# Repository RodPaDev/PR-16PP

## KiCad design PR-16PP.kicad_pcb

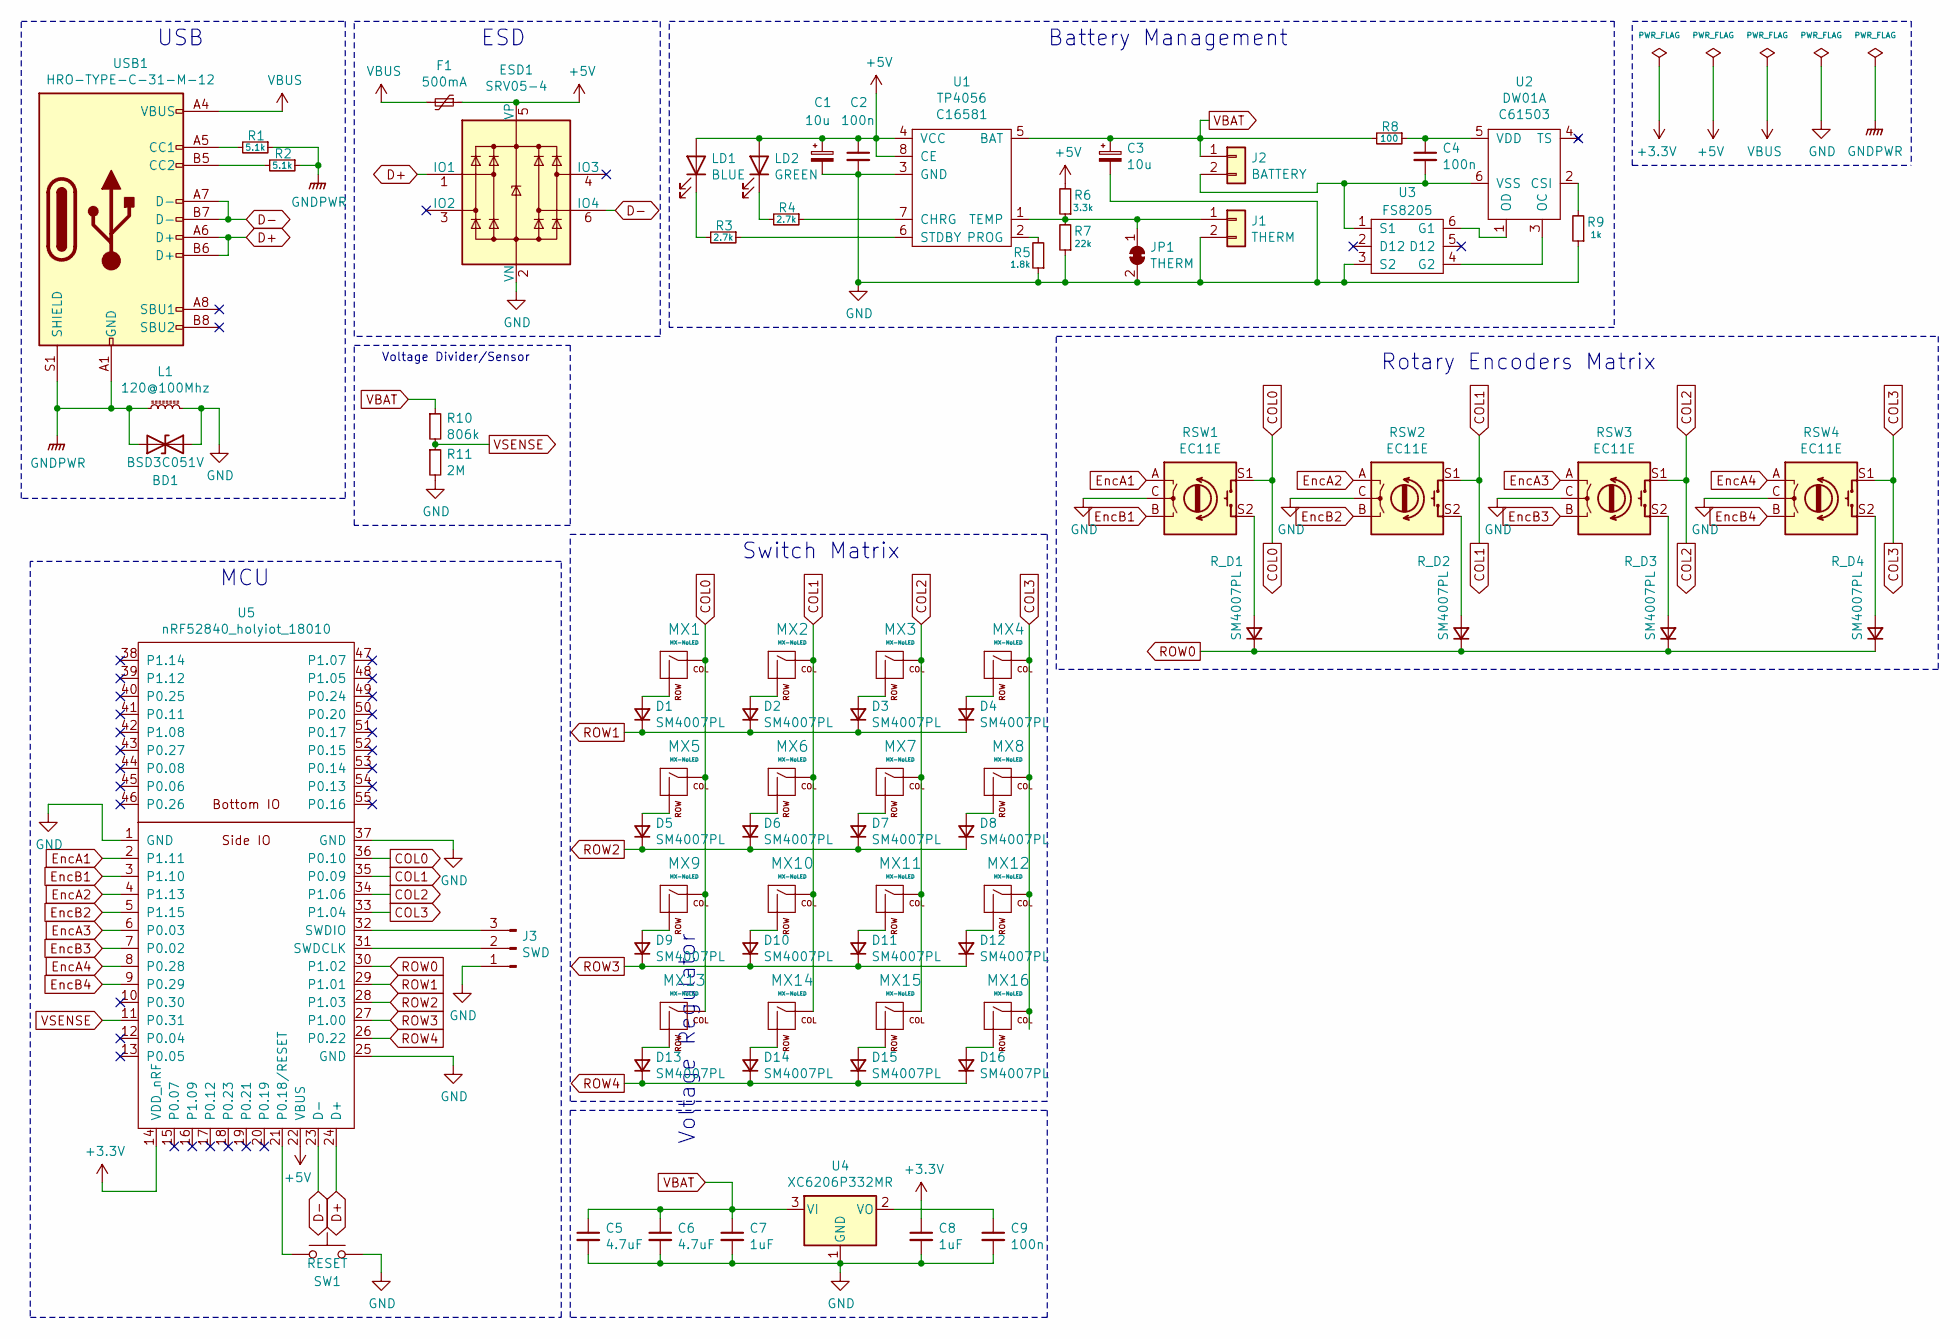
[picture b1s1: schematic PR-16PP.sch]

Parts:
BD1: BSD3C051V; SOT-23_stealth
C1, C3: 10u; C_0603_1608Metric
C2, C4, C9: 100n; C_0603_1608Metric
C5, C6: 4.7uF; C_0603_1608Metric
C7, C8: 1uF; C_0603_1608Metric
D1, D2, D3, D4, D5, D6, D7, D8, D9, D10, D11, D12, D13, D14, D15, D16: SM4007PL; D_SOD-123-Pretty
ESD1: SRV05-4; SOT-23-6
F1: 500mA; Fuse_0603_1608Metric
J1: THERM; JST_SH_SM02B-SRSS-TB_1x02-1MP_P1.00mm_Horizontal
J2: BATTERY; JST_SH_SM02B-SRSS-TB_1x02-1MP_P1.00mm_Horizontal
J3: SWD; PinHeader_1x03_P2.54mm_Vertical
JP1: THERM; SolderJumper-2_P1.3mm_Bridged_RoundedPad1.0x1.5mm
L1: 120@100Mhz; L_0603_1608Metric
LD1: BLUE; LED_0603_1608Metric
LD2: GREEN; LED_0603_1608Metric
MX1, MX2, MX3, MX4, MX5, MX6, MX7, MX8, MX9, MX10, MX11, MX12, MX13, MX14, MX15, MX16: MX-NoLED; MXOnly-1U-Hotswap-Antishear
R1, R2: 5.1k; R_0603_1608Metric
R3, R4: 2.7k; R_0603_1608Metric
R5: 1.8k; R_0603_1608Metric
R6: 3.3k; R_0603_1608Metric
R7: 22k; R_0603_1608Metric
R8: 100; R_0603_1608Metric
R9: 1k; R_0603_1608Metric
R10: 806k; R_0603_1608Metric
R11: 2M; R_0603_1608Metric
RSW1, RSW2, RSW3, RSW4: EC11E; RotaryEncoder_Alps_EC11E-Switch_Vertical_H20mm
R_D1, R_D2, R_D3, R_D4: SM4007PL; D_SOD-123-Pretty
SW1: RESET; SKQG-1155865
U1: TP4056; SOP-8-1EP_4.57x4.57mm_P1.27mm_EP4.57x4.45mm; LCSC C16581
U2: DW01A; SOT-23-6; LCSC C61503
U3: FS8205; SOT-23-6; LCSC C32254
U4: XC6206P332MR; SOT-23; LCSC C5446
U5: nRF52840_holyiot_18010
USB1: HRO-TYPE-C-31-M-12; USB_C_Receptacle_HRO_TYPE-C-31-M-12

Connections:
+3V3: C8.1, U5.14 (VDD_nRF)
+5V: C1.1, C2.1, ESD1.5 (VP), F1.1, LD1.2 (A), LD2.2 (A), R6.2, U1.4 (VCC), U1.8 (CE), U5.22 (VBUS)
COL0: MX1.1 (COL), MX5.1 (COL), MX9.1 (COL), MX13.1 (COL), RSW1.S1, U5.36 (P0.10)
COL1: MX2.1 (COL), MX6.1 (COL), MX10.1 (COL), MX14.1 (COL), RSW2.S1, U5.35 (P0.09)
COL2: MX3.1 (COL), MX7.1 (COL), MX11.1 (COL), MX15.1 (COL), RSW3.S1, U5.34 (P1.06)
COL3: MX4.1 (COL), MX8.1 (COL), MX12.1 (COL), MX16.1 (COL), RSW4.S1, U5.33 (P1.04)
D+: ESD1.1 (IO1), U5.24 (D+), USB1.A6 (D+), USB1.B6 (D+)
D-: ESD1.6 (IO4), U5.23 (D-), USB1.A7 (D-), USB1.B7 (D-)
EncA1: RSW1.A, U5.2 (P1.11)
EncA2: RSW2.A, U5.4 (P1.13)
EncA3: RSW3.A, U5.6 (P0.03)
EncA4: RSW4.A, U5.8 (P0.28)
EncB1: RSW1.B, U5.3 (P1.10)
EncB2: RSW2.B, U5.5 (P1.15)
EncB3: RSW3.B, U5.7 (P0.02)
EncB4: RSW4.B, U5.9 (P0.29)
GND: BD1.2 (A2), C1.2, C2.2, C3.2, C5.2, C6.2, C7.2, C8.2, C9.2, ESD1.2 (VN), J1.2, J3.1, JP1.2 (B), L1.2, R5.1, R7.1, R9.1, R11.2, RSW1.C, RSW2.C, RSW3.C, RSW4.C, SW1.2, U1.3 (GND), U3.3 (S2), U4.1 (GND), U5.1 (GND), U5.25 (GND), U5.37 (GND)
GNDPWR: BD1.1 (A1), L1.1, R1.1, R2.1, USB1.A1 (GND), USB1.A12 (GND), USB1.B1 (GND), USB1.B12 (GND), USB1.S1 (SHIELD)
unnamed: C4.1, R8.1, U2.5 (VDD)
unnamed: C4.2, J2.2, U2.6 (VSS), U3.1 (S1)
unnamed: C9.1, U4.2 (VO)
unnamed: D1.2 (A), MX1.2 (ROW)
unnamed: D2.2 (A), MX2.2 (ROW)
unnamed: D3.2 (A), MX3.2 (ROW)
unnamed: D4.2 (A), MX4.2 (ROW)
unnamed: D5.2 (A), MX5.2 (ROW)
unnamed: D6.2 (A), MX6.2 (ROW)
unnamed: D7.2 (A), MX7.2 (ROW)
unnamed: D8.2 (A), MX8.2 (ROW)
unnamed: D9.2 (A), MX9.2 (ROW)
unnamed: D10.2 (A), MX10.2 (ROW)
unnamed: D11.2 (A), MX11.2 (ROW)
unnamed: D12.2 (A), MX12.2 (ROW)
unnamed: D13.2 (A), MX13.2 (ROW)
unnamed: D14.2 (A), MX14.2 (ROW)
unnamed: D15.2 (A), MX15.2 (ROW)
unnamed: D16.2 (A), MX16.2 (ROW)
unnamed: J1.1, JP1.1 (A), R6.1, R7.2, U1.1 (TEMP)
unnamed: J3.2, U5.31 (SWDCLK)
unnamed: J3.3, U5.32 (SWDIO)
unnamed: LD1.1 (K), R3.2
unnamed: LD2.1 (K), R4.2
unnamed: R1.2, USB1.A5 (CC1)
unnamed: R2.2, USB1.B5 (CC2)
unnamed: R3.1, U1.6 (STDBY)
unnamed: R4.1, U1.7 (CHRG)
unnamed: R5.2, U1.2 (PROG)
unnamed: R9.2, U2.2 (CSI)
unnamed: RSW1.S2, R_D1.2 (A)
unnamed: RSW2.S2, R_D2.2 (A)
unnamed: RSW3.S2, R_D3.2 (A)
unnamed: RSW4.S2, R_D4.2 (A)
unnamed: SW1.1, U5.21 (P0.18/RESET)
unnamed: U2.1 (OD), U3.6 (G1)
unnamed: U2.3 (OC), U3.4 (G2)
ROW0: R_D1.1 (K), R_D2.1 (K), R_D3.1 (K), R_D4.1 (K), U5.30 (P1.02)
ROW1: D1.1 (K), D2.1 (K), D3.1 (K), D4.1 (K), U5.29 (P1.01)
ROW2: D5.1 (K), D6.1 (K), D7.1 (K), D8.1 (K), U5.28 (P1.03)
ROW3: D9.1 (K), D10.1 (K), D11.1 (K), D12.1 (K), U5.27 (P1.00)
ROW4: D13.1 (K), D14.1 (K), D15.1 (K), D16.1 (K), U5.26 (P0.22)
VBAT: C3.1, C5.1, C6.1, C7.1, J2.1, R8.2, R10.1, U1.5 (BAT), U4.3 (VI)
VBUS: F1.2, USB1.A4 (VBUS), USB1.A9 (VBUS), USB1.B4 (VBUS), USB1.B9 (VBUS)
VSENSE: R10.2, R11.1, U5.11 (P0.31)

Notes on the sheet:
Battery Management
USB
Voltage Regulator
Switch Matrix
MCU
Voltage Divider/Sensor
Rotary Encoders Matrix
ESD

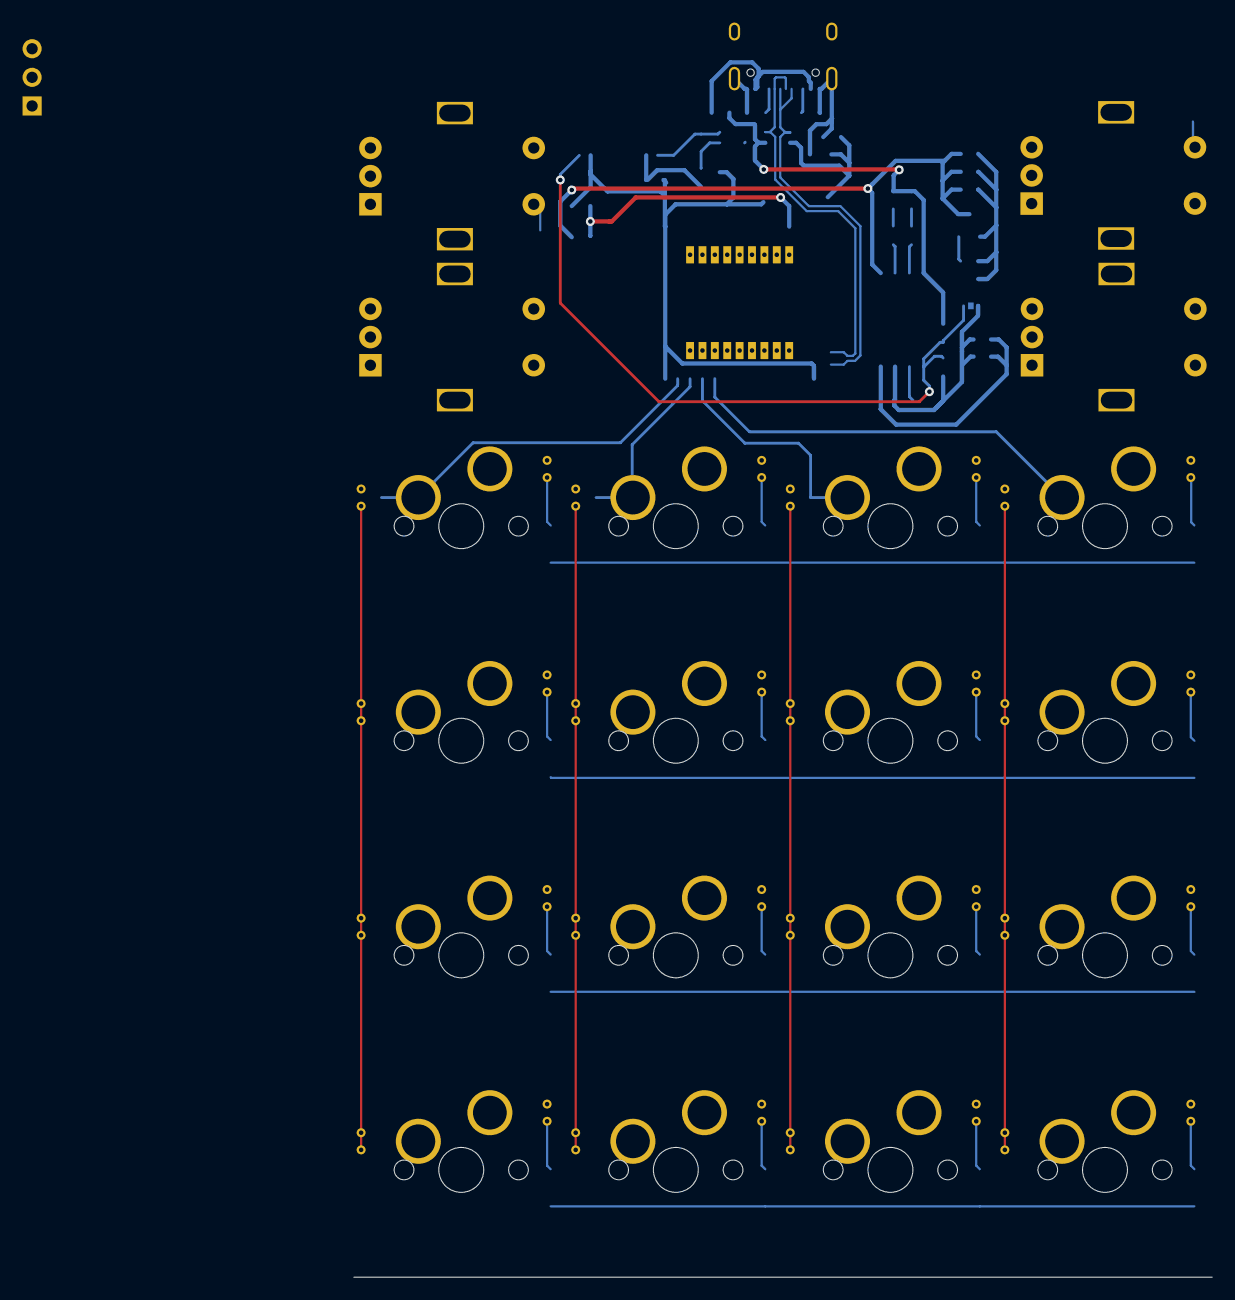
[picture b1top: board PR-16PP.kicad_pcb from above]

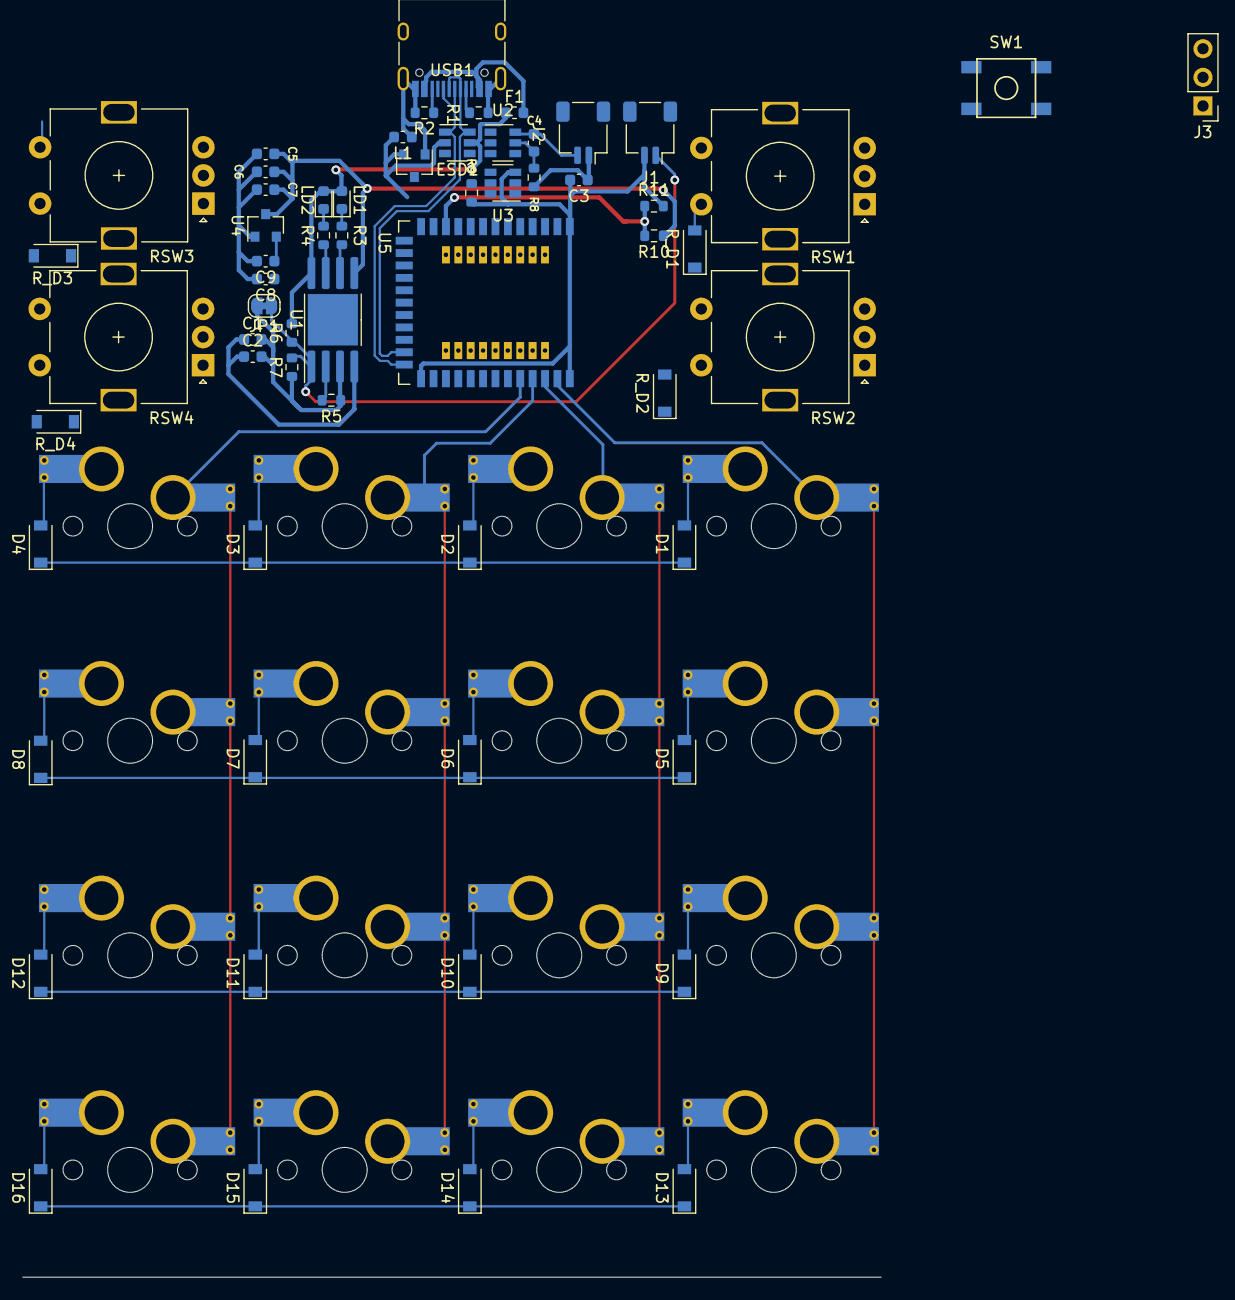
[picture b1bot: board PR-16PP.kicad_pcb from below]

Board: 2 copper layers, 77 parts (61 on the bottom side), 63 nets.

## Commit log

2021-10-20 intial commit
2021-10-20 finish basic schematic
